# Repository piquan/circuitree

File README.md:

# Christmas tree circuit

Merry Christmas!  This is a fun little Christmas decoration that I
created as a gift to friends and family: a small circuit board in the
shape of a Christmas tree, with flashing lights and decorative
buttons, and a stand with has an optional nameplate.

I designed and programmed this from scratch for my closest friends and
family.  It’s taken me several months of engineering, but it’s been a
lot of fun, and I learned a lot of new things while I built it.  It’s
conceptually inspired by a similar circuit that Dad and I built in the
80s from a magazine article, but this circuit uses completely
different modern technology.  I sent my blueprints to [Macrofab, a
factory in Houston](https://macrofab.com/) to create the circuit
boards, and to [Jinxbot, a one-man 3D printing company in Mountain
View](https://jinxbot.com/) to create the stands.  I hand-programmed
and signed each circuit board.  In the four months I spent creating
this, I went through three revisions of the circuit board (plus
several smaller test designs), four revisions of the stand, and
hundreds of revisions of the program.  I hope you enjoy the Christmas
lights in your home as much as I’ve enjoyed creating it!

# Contributing

The entire project is open-source; you're encouraged to modify and
improve it.  Many of my friends are makers, so I want to make sure
that they can have extra fun by reading the details.  The project is
controlled by an ATtiny84A, so you can edit and upload the code right
from the Arduino IDE!  The firmware, debugging device, schematics, PCB
design, and decorative artwork is all in GitHub.

If you just want to look at the schematics and don't have KiCAD, you
can go to the "releases" tab in GitHub and download a zip file with
PDFs of the schematic and PCB, Gerber files for the PCB, .hex files
for the firmware, and .stl and .png files of the stand.

For technical documentation, visit the wiki.  There are notes there
about design decisions I've made, how to reprogram the Christmas tree,
and other useful information for makers.

Contributions are very welcome!  The best way to contribute is to open
a pull request or issue on GitHub.

# Credits

The schematic, PCB layout, decorative artwork, and firmware were all
designed by Joel Holveck.

The tlc5947.h LED driver controller library was originally written by
Limor Fried/Ladyada for Adafruit Industries, at
<https://github.com/adafruit/Adafruit_TLC5947/>.  The version included
here has several changes to use less memory, because of the needs of
the ATtiny environment.  I used Adafruit products (such as the
[TLC5947 breakout board](https://www.adafruit.com/product/1429)
extensively during the development of this project, and am very
grateful both for their product line and open-source contributions.

The capsense.h capacitive touch sensor library was inspired by the
library created by Paul Bagder as maintained by Paul Stoffregen, at
<https://github.com/PaulStoffregen/CapacitiveSensor/>.  The
implementation here is completely new, but borrows several ideas from
the Badger/Stoffregen library.  The Badger/Stoffregen capacitive touch
library is a very simple, straightforward capacitive touch sensing
library; seeing the way it was used helped convince me that the design
was viable.

# License

This project is copyright 2018 by Joel Ray Holveck.  All rights
reserved.

Different parts of this project are licensed differently; the licenses
are in the individual directories.  Generally, firmware is under
GPLv3, the PCB is under the CERN OHL, and the decorative artwork is
under CC-BY-SA.

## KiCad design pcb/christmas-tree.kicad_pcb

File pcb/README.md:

# PCB files

These are the files for the electrical schematic and PCB.

These files are in KiCAD format.  If you check out this directory, you
should be able to open christmas-tree.pro in KiCAD to see the
schematic and PCB layout.

The decorative artwork (and a few custom footprints) are included in
the christmas-tree.pretty directory.  The original SVG files used to
produce the decorative artwork are in the GitHub repository in the
decorations subdirectory.

If you just want to view the schematics or PCB layout files, they are
available in PDF format in the [release
ZIP](https://github.com/piquan/christmas-tree/releases/download/r4.0/Christmas-Tree-r4.zip).

The bill of materials is not included in my KiCAD files.  The BOM I
actually used is
[in the wiki](https://github.com/piquan/christmas-tree/wiki/Bill-of-materials).
That wiki page also includes a few notes about why I chose particular
components, but I don't yet have full documentation about the
components' design constraints.

# License

Copyright (C) 2018 Joel Ray Holveck.  All rights reserved.

This circuit is licensed under the CERN OHL, version 1.2.  The full
license is available in LICENSE.txt.  If you wish to distribute a
modified design, please update CHANGES.txt accordingly.

The requirements of section 3.1 of the CERN OHL require you to
maintain my original copyright and URL on the silkscreen of the PCB.
If you want a special exemption from these requirements, and your
modified PCB will include a clear traceable path to the original
project, I might approve a change to this text.  (For instance,
forking my GitHub project and changing the URL to your fork is likely
to be okay.)  In this case, contact me to request an excemption.

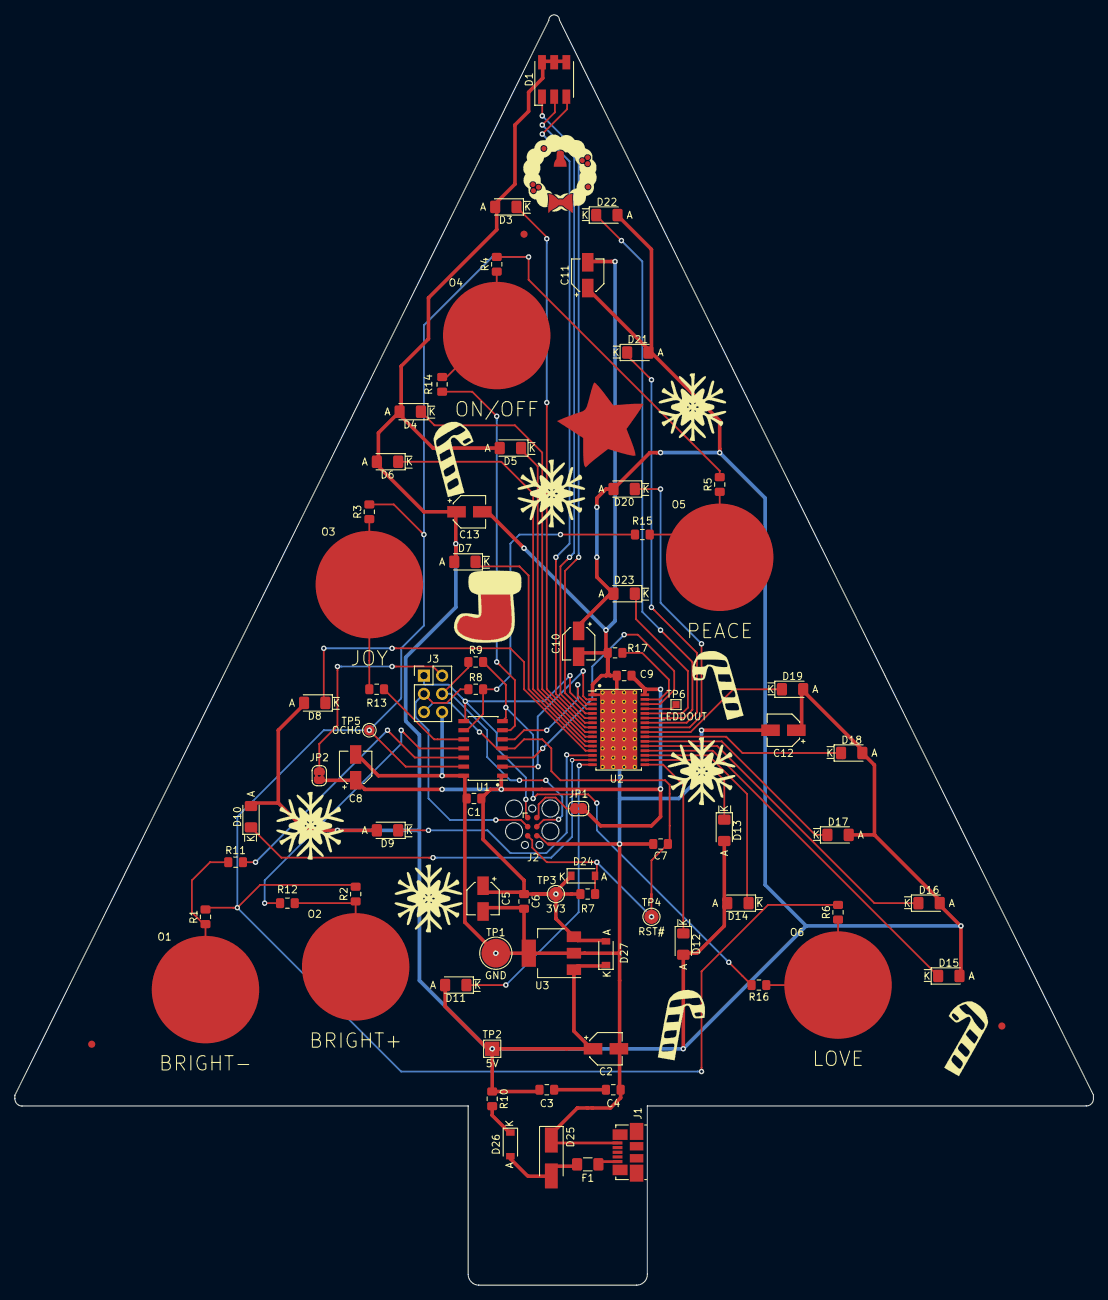
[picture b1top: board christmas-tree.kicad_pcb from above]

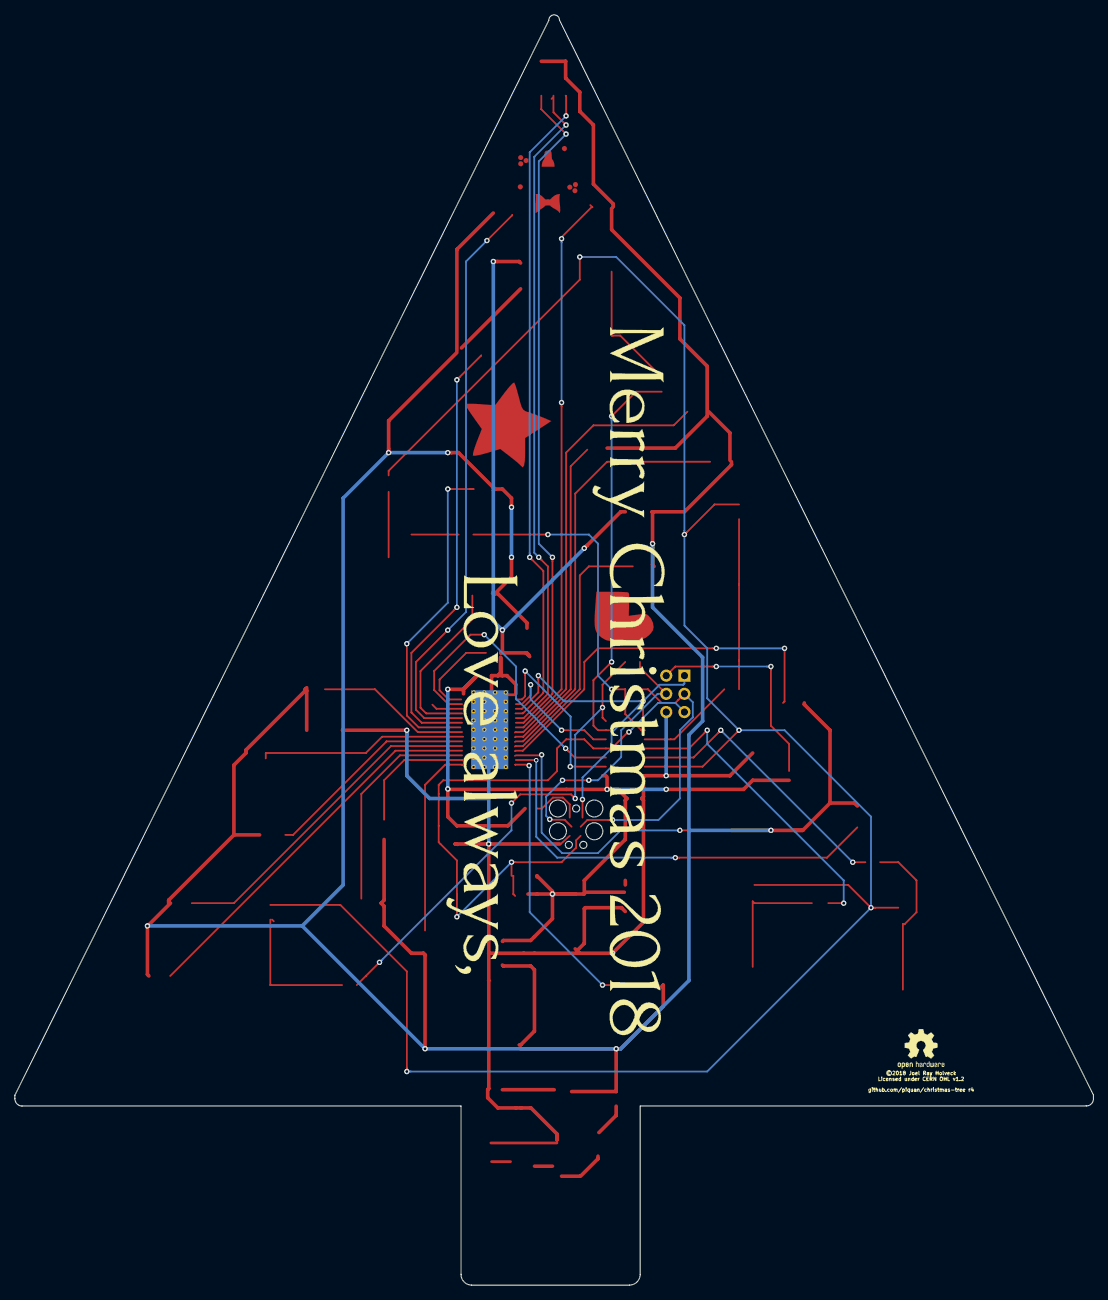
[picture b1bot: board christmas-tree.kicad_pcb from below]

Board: 2 copper layers, 150.5 x 177.2 mm, 95 parts (3 on the bottom side), 55 nets.

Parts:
C1, C9: 0.1uF; C_0805_2012Metric_Pad1.15x1.40mm_HandSolder
C2, C5, C8, C10, C11, C12, C13: 3.3uF; CP_Elec_4x5.4
C3, C4, C6, C7: DNP; C_0805_2012Metric_Pad1.15x1.40mm_HandSolder
D1: LED_RGB; LED_RGB_5050-6
D3, D7, D11, D15, D19, D23: LTST-C150KRKT; LED_1206_Wurth_AK
D4, D8, D12, D16, D20: LTST-C150KSKT; LED_1206_Wurth_AK
D5, D9, D13, D17, D21: LTST-C150TBKT; LED_1206_Wurth_AK
D6, D10, D14, D18, D22: LTST-C150KGKT; LED_1206_Wurth_AK
D24, D26: MBR0520L; D_SOD-123_AK
D25: SMAJ7.0CA; D_SMA_Handsoldering
D27: DNP; D_SOD-123_AK
DORN1: SYM_Arrow45_Tiny; star
DORN2: SYM_Arrow45_Tiny; stocking
DORN3, DORN5: SYM_Arrow45_Tiny; candy-cane
DORN4, DORN6: SYM_Arrow45_Tiny; candy-cane-mirror
DORN7, DORN8, DORN9, DORN10, DORN11: SYM_Arrow45_Tiny; snowflake
DORN12: SYM_Arrow45_Tiny; OSHW-Logo2_7.3x6mm_SilkScreen
DORN13: SYM_Arrow45_Tiny; wreath
F1: 500mA; Fuse_1206_3216Metric_Pad1.42x1.75mm_HandSolder
FID1, FID2, FID3: SYM_Arrow45_Tiny; Fiducial_1mm_Dia_2.54mm_Outer_CopperTop
J1: USB_B_Micro; USB_Micro-B_Molex_47346-0001
J2: TC2030; Tag-Connect_TC2030-IDC-FP_2x03_P1.27mm_Vertical
J3: AVR-ISP-6; PinHeader_2x03_P2.54mm_Vertical
JP1: JCPWR; SolderJumper-2_P1.3mm_Bridged2Bar_RoundedPad1.0x1.5mm
JP2: ISPPWR; SolderJumper-2_P1.3mm_Bridged2Bar_RoundedPad1.0x1.5mm
LOGO1: Logo_Merry_Christmas; merry-christmas
LOGO2: Logo_Merry_Christmas; love-always
O1: BRIGHT-; TestPoint_Pad_D15.0mm
O2: BRIGHT+; TestPoint_Pad_D15.0mm
O3: JOY; TestPoint_Pad_D15.0mm
O4: ON/OFF; TestPoint_Pad_D15.0mm
O5: PEACE; TestPoint_Pad_D15.0mm
O6: LOVE; TestPoint_Pad_D15.0mm
R1, R2, R3, R4, R5, R6: 1M; R_0805_2012Metric_Pad1.15x1.40mm_HandSolder
R7: 10K; R_0805_2012Metric_Pad1.15x1.40mm_HandSolder
R8, R9: 100; R_0805_2012Metric_Pad1.15x1.40mm_HandSolder
R10: 0; R_0805_2012Metric_Pad1.15x1.40mm_HandSolder
R11, R12, R13, R14, R15, R16: 50; R_0805_2012Metric_Pad1.15x1.40mm_HandSolder
R17: 2.7K; R_0805_2012Metric_Pad1.15x1.40mm_HandSolder
TP1: GND; TestPoint_Pad_D4.0mm
TP2: 5V; TestPoint_Pad_2.0x2.0mm
TP3: 3V3; TestPoint_Pad_D2.0mm
TP4: RST#; TestPoint_Pad_D2.0mm
TP5: OCHG; TestPoint_Pad_D1.5mm
TP6: LEDDOUT; TestPoint_Pad_1.0x1.0mm
U1: ATtiny84A-20SSU; SOIC-14_3.9x8.7mm_P1.27mm
U2: TLC5947DAP; HTSSOP-32-1EP_6.1x11mm_P0.65mm_EP5.2x11mm_Mask4.11x4.36mm_T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
U3: LT1129CST-3.3; SOT-223-3_TabPin2

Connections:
+3V3: C1.2, C5.1, C6.1, C8.1, C9.2, D24.1, D27.2, JP1.1, JP2.1, R7.1, TP3.1, U1.1, U2.32, U3.3
+5V: C2.1, C3.1, C10.1, C11.1, C12.1, C13.1, D1.4, D1.5, D1.6, D3.2, D4.2, D5.2, D6.2, D7.2, D8.2, D9.2, D10.2, D11.2, D12.2, D13.2, D14.2, D15.2, D16.2, D17.2, D18.2, D19.2, D20.2, D21.2, D22.2, D23.2, D27.1, R10.1, TP2.1, U3.1
/BLANK: U1.2, U2.2
/IREF: R17.1, U2.31
/ISPMOSI: J2.4, J3.4, R9.1
/ISPSCK: J2.3, J3.3, R8.1
/LEDCLK: U1.5, U2.3
/LEDDOUT: TP6.1, U2.29
/MISO: J2.1, J3.1, U1.8, U2.4
/MOSI: R9.2, R16.2, U1.7
/O1S: R11.2, U1.12
/O2S: R12.2, U1.11
/O3S: R13.2, U1.10
/O4S: R14.2, U1.6
/OCHG: R1.2, R2.2, R3.2, R4.2, R5.2, R6.2, TP5.1, U1.13
/RST#: C7.1, D24.2, J2.5, J3.5, R7.2, TP4.1, U1.4
/SCK: R8.2, R15.2, U1.9
/XLAT: U1.3, U2.30
GND: C1.1, C2.2, C4.2, C5.2, C6.2, C7.2, C8.2, C9.1, C10.2, C11.2, C12.2, C13.2, D25.1, J1.5, J2.6, J3.6, R17.2, TP1.1, U1.14, U2.1, U2.33, U3.2
unnamed: C3.2, C4.1
unnamed: D1.1, U2.5
unnamed: D1.2, U2.6
unnamed: D1.3, U2.7
unnamed: D3.1, U2.8
unnamed: D4.1, U2.9
unnamed: D5.1, U2.10
unnamed: D6.1, U2.11
unnamed: D7.1, U2.12
unnamed: D8.1, U2.13
unnamed: D9.1, U2.14
unnamed: D10.1, U2.15
unnamed: D11.1, U2.16
unnamed: D12.1, U2.17
unnamed: D13.1, U2.18
unnamed: D14.1, U2.19
unnamed: D15.1, U2.20
unnamed: D16.1, U2.21
unnamed: D17.1, U2.22
unnamed: D18.1, U2.23
unnamed: D19.1, U2.24
unnamed: D20.1, U2.25
unnamed: D21.1, U2.26
unnamed: D22.1, U2.27
unnamed: D23.1, U2.28
unnamed: D25.2, D26.2, F1.1
unnamed: D26.1, R10.2
unnamed: F1.2, J1.1
unnamed: J2.2, JP1.2
unnamed: J3.2, JP2.2
unnamed: O1.1, R1.1, R11.1
unnamed: O2.1, R2.1, R12.1
unnamed: O3.1, R3.1, R13.1
unnamed: O4.1, R4.1, R14.1
unnamed: O5.1, R5.1, R15.1
unnamed: O6.1, R6.1, R16.1

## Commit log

2018-10-28 Initial commit.
    Sorry I didn't commit my drafts before this. This revision is
    destined to be named r3; the earlier revisions didn't get built. Now
    I'm getting closer to something I'd like to share. It would have been
    nice to commit my earlier revs so that people can see what the process
    was, but I just didn't have time.
2018-10-29 Changes made while preparing r3
2018-10-29 Add licenses
2018-11-12 Change the base to a pile of presents
2018-11-13 Bug fixes and debugging changes
    Remove some debugging code that forces the cap sensors to max value.
    Make the cap sense POST set the pin modes, so they can work even when the debugger has changed the pin modes.
    Fix a bug that made the blanking state only toggle once, then stay blank forever.
    Disable by default the option to cause the JOY button to always burn all LEDs.
    Move the Debugger declaration to above my own #includes, so I can use Debugger in them.
    Declare DoSanity to be a friend function of TLC5947, so it can check the pwmbuffer values; some failure modes can be detected by looking at them.
2018-11-15 Have Peace mode keep a constant brightness in each spectral channel.
    This required many other changes to make more space, and I also did
    some debugging stuff and other cleanups too.
2018-11-15 Small, mostly-inconsequential cleanups
2018-11-27 More changes to complete r4 of the PCB.
    Change the wreath to a new design. Export it at a higher DPI (600)
    before importing it into KiCAD; that was a big problem with the old
    rev (which had a 200 DPI export).
    Move the "Love Always" around a bit, and a few other tiny tweaks.
    No substantial changes since r3.
    Update the title blocks, silkscreened copyright notice, and metadata
2018-11-27 Add operator[] and clear() methods.
    operator[] is just for simplicity. clear() is to replace all the "=0"
    loops with a single call.
2018-11-27 Add a new JOY sub-mode, tweak brightness, and shrink the executable a lot.
    CTDebugger no longer inherits from Print. The integer print routines
    now print in hex, since the Print decimal print routines take up way
    too much executable space. This saves about 1.5k.
    Add support for JOY submodes. This lets me put different display
    hacks under the JOY mode, and cycle through them by tapping on the JOY
    button repeatedly. Currently, only two sub-modes are implemented.
2018-11-27 Rename the "base" to the "stand", which is less ambiguous.
2018-11-27 Add back some diagnostics which were previously removed for space.
    After changing CTDebugger to print in hex, I've got lots more space free.
2018-12-02 Add CTDebugger:print(float) and (double)
    These use hex representations that are similar to C++11's %a, but show
    the exponent in hex for smaller code size.
2018-12-03 Improve handling of name plaques on the stand.
2018-12-07 Make joy_sub_mode an enum, and fix an overflow in the double-chase mode
2018-12-08 Enable the LED test, improve the joy phase lights, cache build products
2018-12-08 Initial revision
2018-12-08 Tweak the slot width a bit more
2018-12-08 New sub-mode kSubModeCylonFill
    Make the default Joy mode kSubModeDoubleChase
    Rearrange to save a few bytes of flash here and there
    Switch kSubModeDoubleChase to use the same RGB LED driver as Peace and
    Love
    Decrease how fast BRIGHT+ and BRIGHT- taps work
2018-12-09 Adjust the compile command
    Include the progress bar during flash, and remove the path to arduino.
2018-12-09 Speed up the flash.
    I haven't tested this much, but it works for me.
2018-12-09 Add .gitignores for some build products
2018-12-09 Improve the README
2018-12-09 Move the image
2018-12-11 Moved notes and parts list to the GitHub wiki
    notes.txt was moved pretty much verbatim to https://github.com/piquan/christmas-tree/wiki/Design-notes .
    parts.txt had some random notes about the parts I'm picking; I replaced it with the final BOM at https://github.com/piquan/christmas-tree/wiki/Bill-of-Materials .
2018-12-13 Improve comments on schematic
2018-12-22 Improve documentation and clarify licenses

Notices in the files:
pcb/christmas-tree.kicad_pcb:
©2018 Joel Ray Holveck
Licensed under CERN OHL v1.2
